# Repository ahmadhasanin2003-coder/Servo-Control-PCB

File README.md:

# Servo-Control-PCB

A simple servo control circuit designed using the **NE555 timer IC**.

## Overview

This project generates a variable control signal for a servo using a 555 timer configured as an astable/pulse-generation circuit.

The servo position can be adjusted using a potentiometer, which changes the timing characteristics of the generated signal.

## Components

- NE555 Timer IC
- Potentiometer
- 1N4148 Diode
- LED
- Resistors
- Capacitor
- External power and servo connections

## Working Principle

The NE555 generates a periodic pulse signal. The potentiometer changes the charging/discharging timing of the capacitor, which changes the pulse characteristics supplied to the servo.

By adjusting the potentiometer, the servo position can be controlled.

## Tools Used

- KiCad
- NE555 Timer

## Project Files

The `hardware` directory contains the KiCad design files:

- `.kicad_pro` — KiCad project
- `.kicad_sch` — Schematic
- `.kicad_pcb` — PCB layout

## Status

**Schematic:** Completed  
**PCB:** In progress

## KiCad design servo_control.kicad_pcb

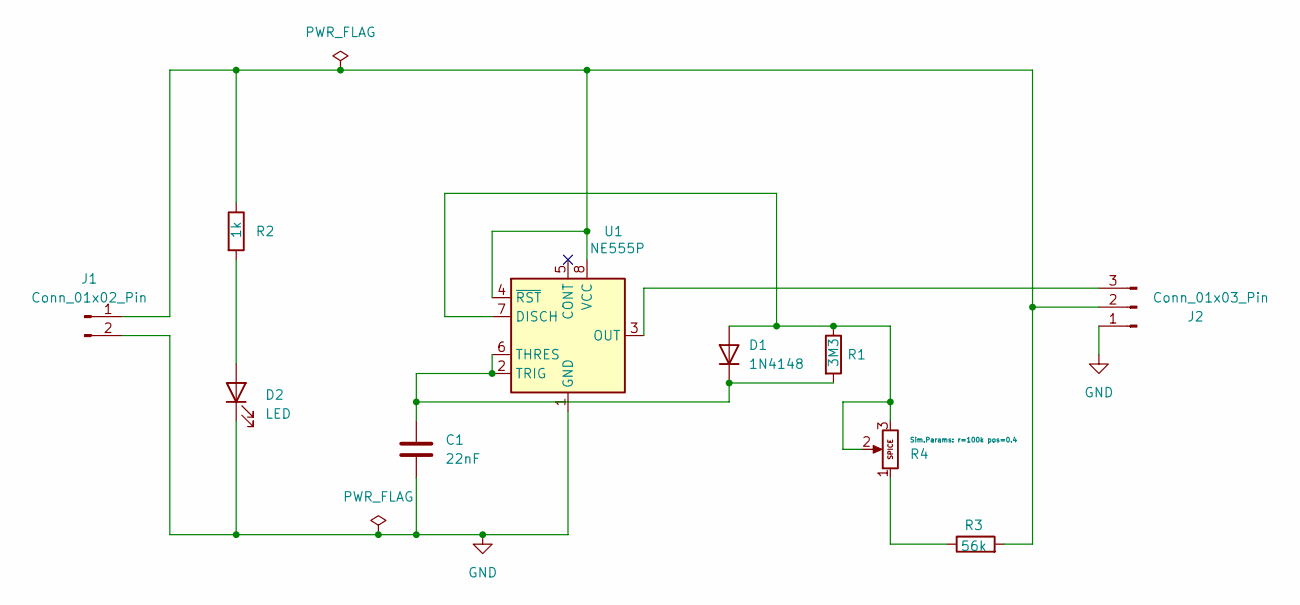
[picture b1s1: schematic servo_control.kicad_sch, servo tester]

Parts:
C1: 22nF; C_Disc_D4.3mm_W1.9mm_P5.00mm
D1: 1N4148; D_DO-35_SOD27_P7.62mm_Horizontal
D2: LED; LED_D3.0mm
J1: Conn_01x02_Pin; PinHeader_1x02_P2.54mm_Horizontal
J2: Conn_01x03_Pin; PinHeader_1x03_P2.54mm_Horizontal
R1: 3M3; R_Axial_DIN0204_L3.6mm_D1.6mm_P7.62mm_Horizontal
R2: 1k; R_Axial_DIN0204_L3.6mm_D1.6mm_P7.62mm_Horizontal
R3: 56k; R_Axial_DIN0204_L3.6mm_D1.6mm_P7.62mm_Horizontal
R4: Potentiometer; Potentiometer_Alps_RK163_Single_Horizontal
U1: NE555P; DIP-8_W7.62mm

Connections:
GND: C1.2, D2.1 (K), J1.2, J2.1, U1.1 (GND)
unnamed: D1.2 (A), R1.1, R4.2, R4.3, U1.7 (DISCH)
unnamed: C1.1, D1.1 (K), R1.2, U1.2 (TRIG), U1.6 (THRES)
unnamed: D2.2 (A), R2.2
unnamed: J1.1, J2.2, R2.1, R3.2, U1.4 (~RST), U1.8 (VCC)
unnamed: J2.3, U1.3 (OUT)
unnamed: R3.1, R4.1

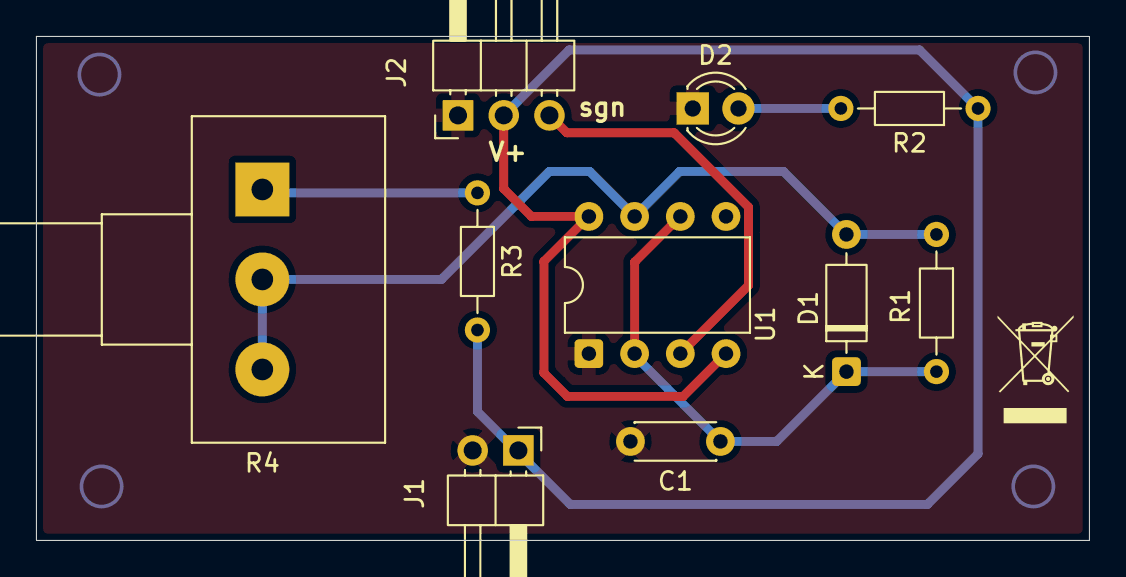
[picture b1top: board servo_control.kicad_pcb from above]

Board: 2 copper layers, 58.5 x 28.0 mm, 10 parts (0 on the bottom side), 7 nets.
